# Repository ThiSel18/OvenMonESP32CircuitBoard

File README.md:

# OvenMonESP32CircuitBoard
KiCad Project for Oven Monitoring

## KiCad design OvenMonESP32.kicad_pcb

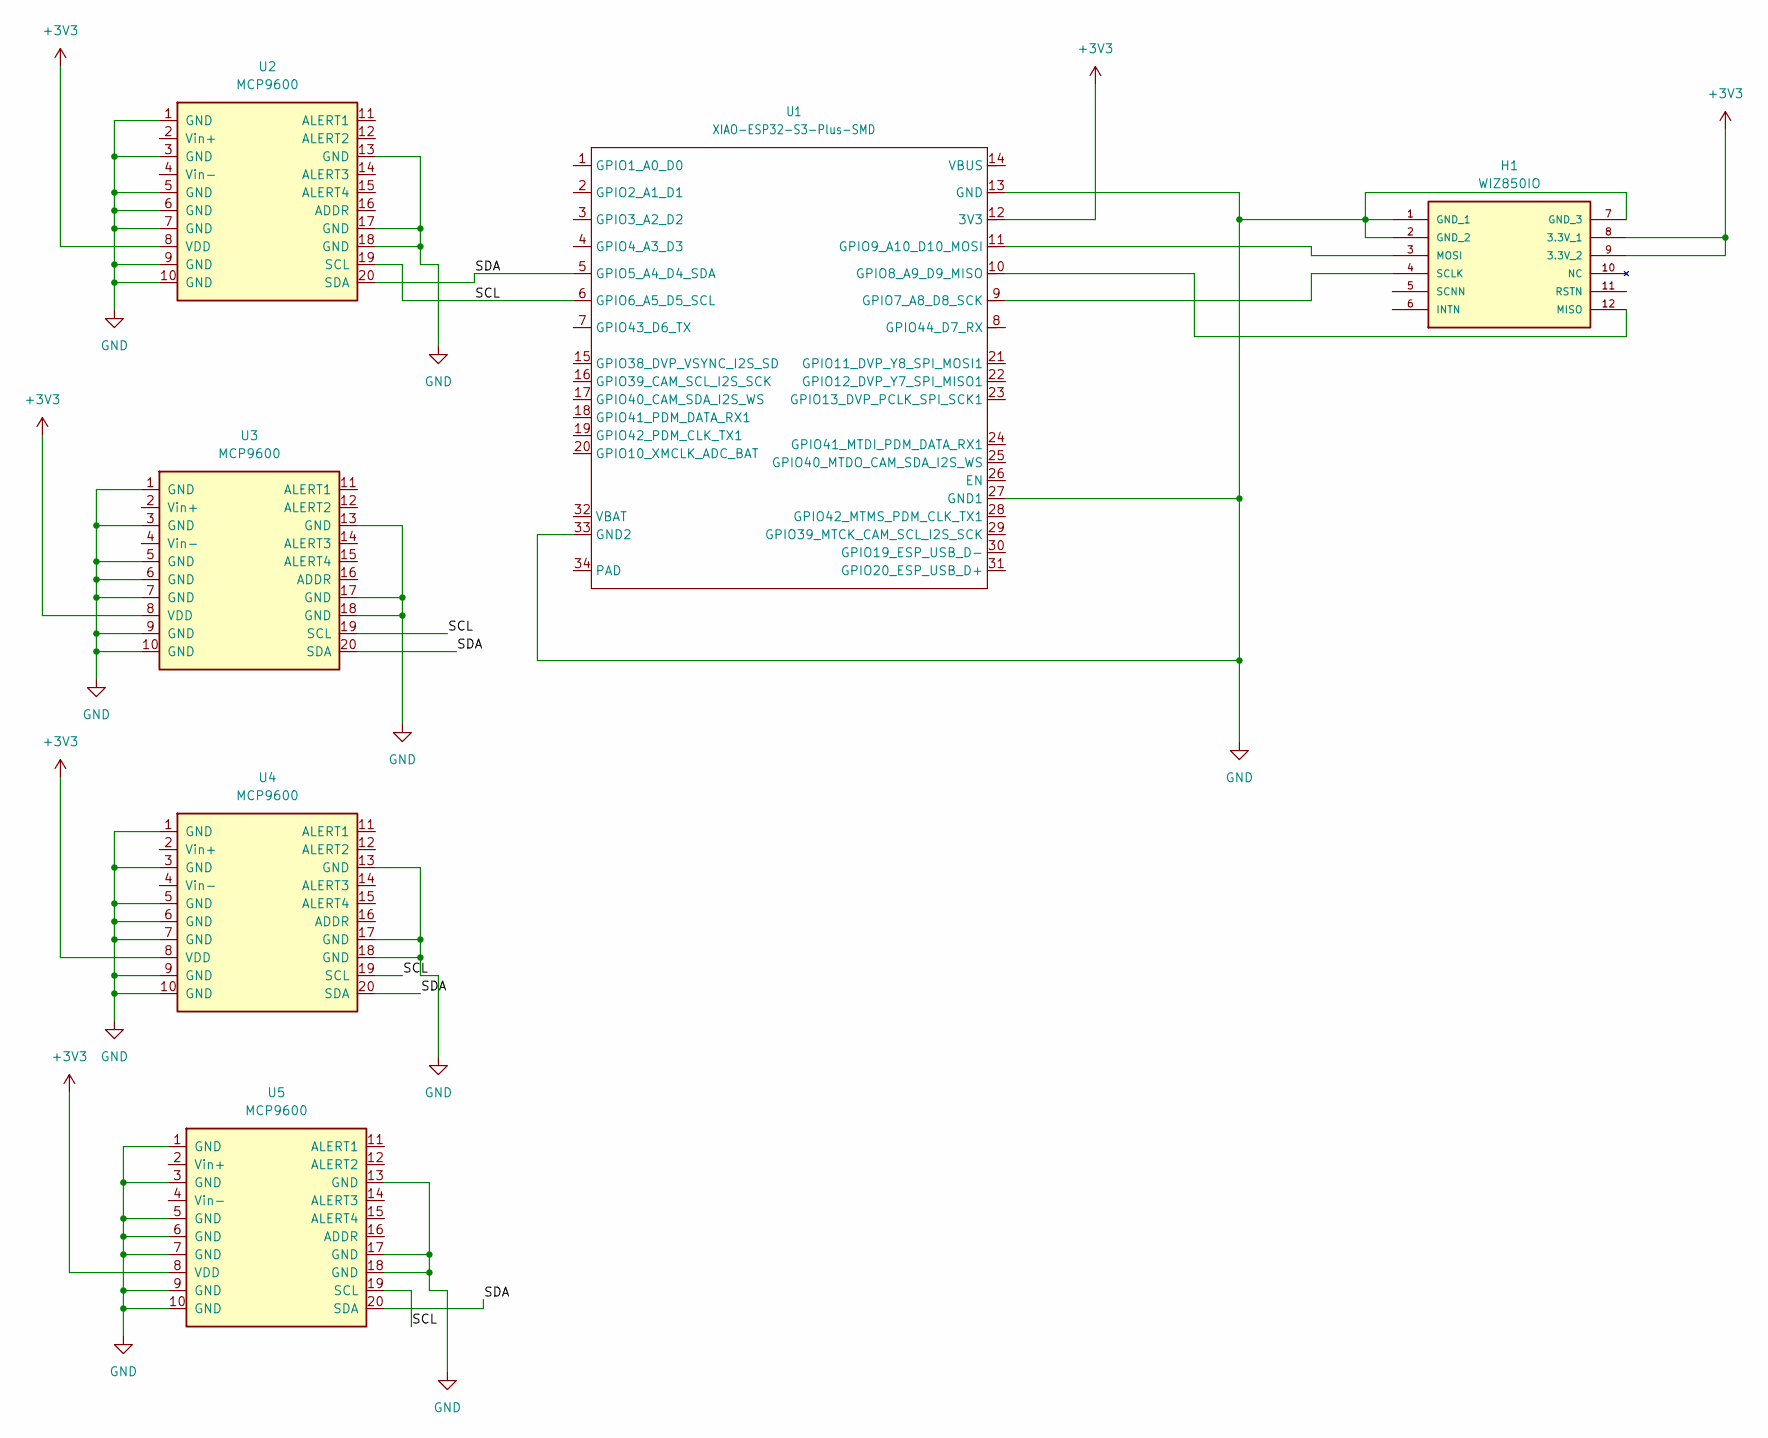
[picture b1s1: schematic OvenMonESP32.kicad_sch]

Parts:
H1: WIZ850IO; MANUFACTURER_PART_NUMBER WIZ850IO
U1: XIAO-ESP32-S3-Plus-SMD
U2, U3, U4, U5: MCP9600; QFN-20-1EP_5x5mm_P0.65mm_EP3.35x3.35mm

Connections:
+3V3: H1.8 (3.3V_1), H1.9 (3.3V_2), U1.12 (3V3), U2.8 (VDD), U3.8 (VDD), U4.8 (VDD), U5.8 (VDD)
/SCL: U1.6 (GPIO6_A5_D5_SCL), U2.19 (SCL), U3.19 (SCL), U4.19 (SCL), U5.19 (SCL)
/SDA: U1.5 (GPIO5_A4_D4_SDA), U2.20 (SDA), U3.20 (SDA), U4.20 (SDA), U5.20 (SDA)
GND: H1.1 (GND_1), H1.2 (GND_2), H1.7 (GND_3), U1.13 (GND), U1.27 (GND1), U1.33 (GND2), U2.1 (GND), U2.3 (GND), U2.5 (GND), U2.6 (GND), U2.7 (GND), U2.9 (GND), U2.10 (GND), U2.13 (GND), U2.17 (GND), U2.18 (GND), U3.1 (GND), U3.3 (GND), U3.5 (GND), U3.6 (GND), U3.7 (GND), U3.9 (GND), U3.10 (GND), U3.13 (GND), U3.17 (GND), U3.18 (GND), U4.1 (GND), U4.3 (GND), U4.5 (GND), U4.6 (GND), U4.7 (GND), U4.9 (GND), U4.10 (GND), U4.13 (GND), U4.17 (GND), U4.18 (GND), U5.1 (GND), U5.3 (GND), U5.5 (GND), U5.6 (GND), U5.7 (GND), U5.9 (GND), U5.10 (GND), U5.13 (GND), U5.17 (GND), U5.18 (GND)
unnamed: H1.12 (MISO), U1.10 (GPIO8_A9_D9_MISO)
unnamed: H1.3 (MOSI), U1.11 (GPIO9_A10_D10_MOSI)
unnamed: H1.4 (SCLK), U1.9 (GPIO7_A8_D8_SCK)

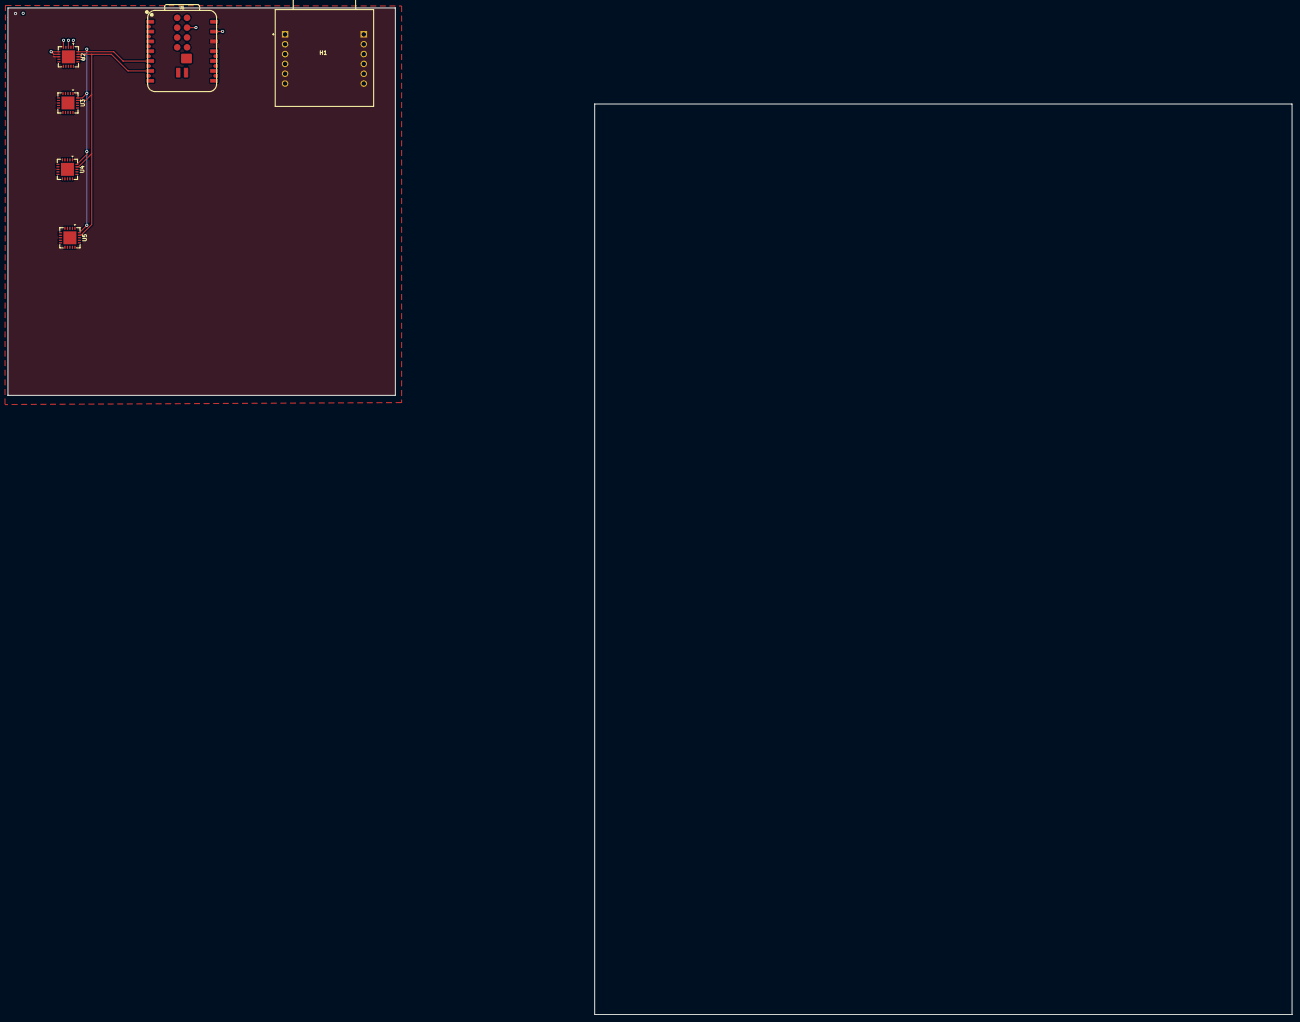
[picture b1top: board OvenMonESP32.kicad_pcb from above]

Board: 4 copper layers, 100.0 x 100.0 mm, 6 parts (0 on the bottom side), 7 nets.

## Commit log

2026-06-16 Add network module
